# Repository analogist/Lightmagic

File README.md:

# Lightmagic
A safety-isolated dual-channel flexible audio and photodiode trigger for electrophysiological recording time synchronization and verification

## Design
The board has 2 inputs: a mono audio trigger (3.5mm / 1/8" jack, stereo combined) and a photodiode.

The photodiode is generally mounted to a screen or other photo synchronization trigger, and its sensitivity is adjustable with a trim pot. It's powered by a single regulated >5V low voltage source, usually a 9V battery. The audio jack is plugged into an audio synchronization trigger, and looks for any (3Hz highpassed) audio input higher than 0.7V. The audio half is powered by a mini-USB cable which may be hooked up to wall AC at some point, and the entire audio input is optically isolated from the photo trigger half of the board.

The output is an additional 3.5mm (1/8") audio jack with the L channel (tip) carrying the (rectified, amplified, isolated) audio trigger signal and the R channel (ring) carrying the (amplified) photodiode signal. Both channel should swing from 0 (off) - 2V (trigger on) with the standard BOM items.

The design allows for this board to be "trigger glue" between a psychophysical presentation (audio or on-screen stimuli) and electrophysiological recording systems when sub-millisecond synchronization is required, such as for neurostimulation. Note that output voltages are still in the 2V range; this should be further reduced as close as possible to the recording system via passive voltage dividers down to safe voltages and currents (hopefully <50μA for all failure conditions) for in-vivo recordings.

## Files

The source Eagle CAD files are in the `eagle` directory.
The OSH Park-compatible `ger` and `xln` files can be found in the `gerber` directory. Zipping it will allow for manufacture.

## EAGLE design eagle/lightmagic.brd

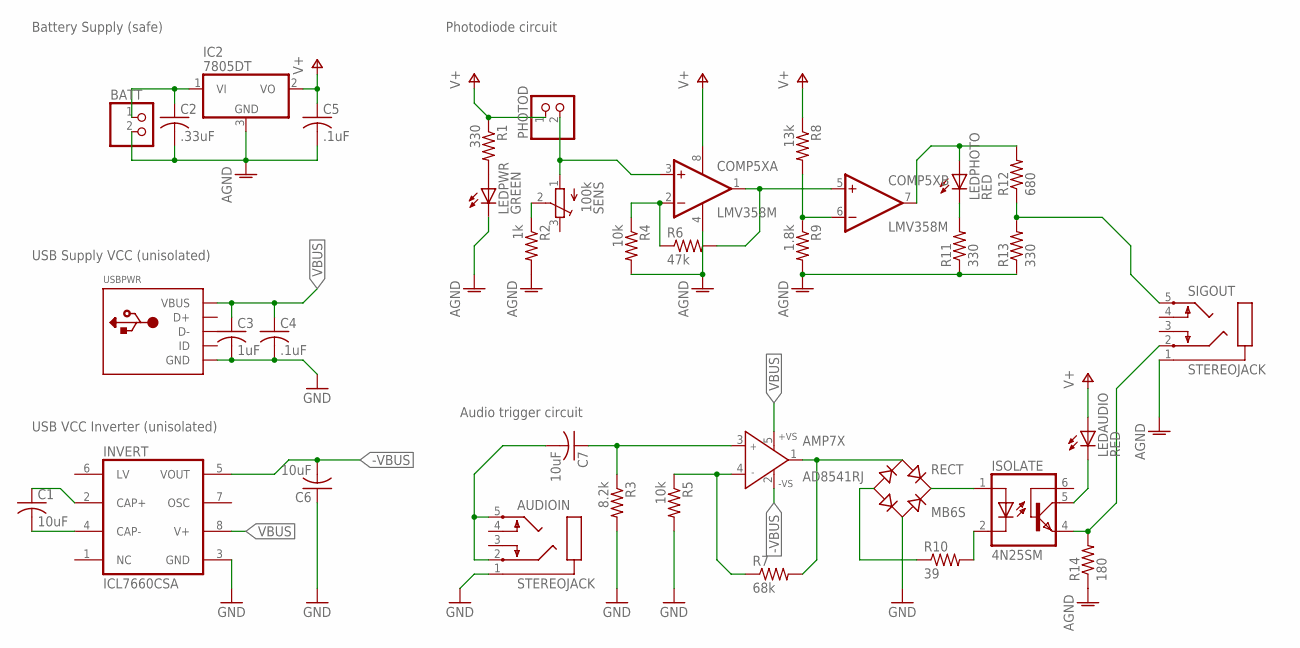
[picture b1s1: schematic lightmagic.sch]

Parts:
AMP7X: AD8541RJ; SOT23-5; MPN AD8541ARTZ-R2
AUDIOIN: STEREOJACK; STX3100; MPN 35RAPC4BHN2
BATT: PINHD-1X2; 1X02; MPN 640456-2
C1, C6, C7: 10uF; C0805; MPN GRT21BR61E106KE13L
C2: .33uF; C0805; MPN MC0805B334K500CT
C3: 1uF; C0805; MPN C0805X104K3RAC3316
C4, C5: .1uF; C0805; MPN 0805YC104KAT2A
COMP5X: LMV358M; SO08; MPN LMV358M
IC2: 7805DT; TO252; MPN MC7805CDTG
INVERT: ICL7660CSA; SO08; MPN LMC7660IM/NOPB
ISOLATE: 4N25SM; DIL6-SMD; MPN 4N25-300E
LEDAUDIO: RED; CHIP-LED0805; MPN QTLP630C7TR
LEDPHOTO: RED; CHIP-LED0805; MPN QTLP630C7TR
LEDPWR: GREEN; CHIP-LED0805; MPN QTLP630C7TR
PHOTOD: PINHD-1X2; 1X02; MPN 640456-2
R1, R11, R13: 330; R0805; MPN ERJ-6ENF3300V
R2: 1k; R0805; MPN ERJ-6ENF12R0V
R3: 8.2k; R0805; MPN MC01W080518K2
R4, R5: 10k; R0805; MPN CRCW080510K0FKTA
R6: 47k; R0805; MPN CRCW080547K0FKEA
R7: 68k; R0805; MPN CRCW080568K0FKEA
R8: 13k; R0805; MPN CRCW080513K0FKEA
R9: 1.8k; R0805; MPN CRCW08051K80FKEA
R10: 39; R0805; MPN ERJ-6GEYJ390V
R12: 680; R0805; MPN ERA-6AEB681V
R14: 180; R0805; MPN CRCW0805180RJNEA
RECT: MB6S; SOIC-4; MPN MB6S
SENS: 100k; TC33X; MPN CRCW0805100KJNEA
SIGOUT: STEREOJACK; STX3100; MPN 35RAPC4BHN2
USBPWR: USBMINIB; USB-MINIB; MPN 1734035-1

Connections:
-VBUS: AMP7X.2 (-VS), C6.2, INVERT.5 (VOUT)
AGND: BATT.2, C2.2, C5.2, COMP5X.4 (V-), IC2.3 (GND), LEDPWR.C, R2.2, R4.2, R9.2, R11.1, R13.1, R14.1, SIGOUT.1
GND: AUDIOIN.1, C3.2, C4.2, C6.1, INVERT.3 (GND), R3.2, R5.2, RECT.~2 (AC2), USBPWR.GND
unnamed: AMP7X.4 (IN-), R5.1, R7.1
unnamed: C1.1, INVERT.2 (CAP+)
unnamed: C1.2, INVERT.4 (CAP-)
unnamed: AUDIOIN.2, AUDIOIN.5, C7.2
unnamed: AMP7X.3 (IN+), C7.1, R3.1
unnamed: AMP7X.1 (OUT), R7.2, RECT.~1 (AC1)
unnamed: ISOLATE.1 (A), RECT.+
unnamed: ISOLATE.2 (C), R10.2
unnamed: R10.1, RECT.-
unnamed: BATT.1, C2.1, IC2.1 (VI)
unnamed: R2.1, SENS.2 (S)
unnamed: LEDPWR.A, R1.2
unnamed: COMP5X.3 (+IN), PHOTOD.2, SENS.1 (A)
unnamed: COMP5X.2 (-IN), R4.1, R6.1
unnamed: COMP5X.1 (OUT), COMP5X.5 (+IN), R6.2
unnamed: COMP5X.6 (-IN), R8.2, R9.1
unnamed: ISOLATE.4 (EMI), R14.2, SIGOUT.2
unnamed: ISOLATE.5 (COL), LEDAUDIO.C
unnamed: LEDPHOTO.C, R11.2
unnamed: R12.1, R13.2, SIGOUT.5
unnamed: COMP5X.7 (OUT), LEDPHOTO.A, R12.2
V+: C5.1, COMP5X.8 (V+), IC2.2 (VO), LEDAUDIO.A, PHOTOD.1, R1.1, R8.1
VBUS: AMP7X.5 (+VS), C3.1, C4.1, INVERT.8 (V+), USBPWR.VBUS

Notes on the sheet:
Battery Supply (safe)
USB VCC Inverter (unisolated)
USB Supply VCC (unisolated)
Photodiode circuit
Audio trigger circuit

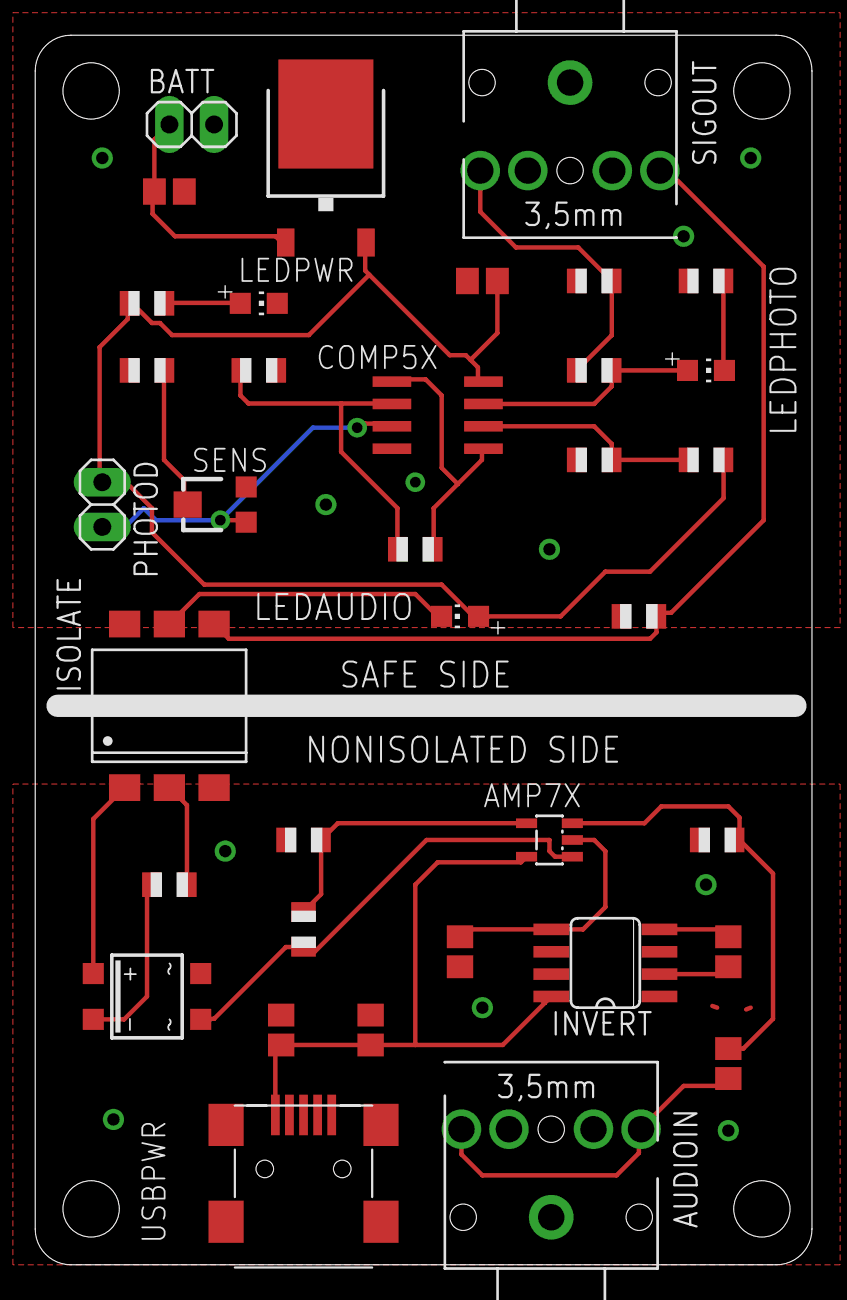
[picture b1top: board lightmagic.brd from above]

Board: 2 copper layers, 44.1 x 69.8 mm, 36 parts (0 on the bottom side), 26 nets.

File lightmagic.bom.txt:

Part     Value      Device          Package      Description                                                                   MF                      MPN                OC_FARNELL OC_NEWARK
AMP7X    AD8541RJ   AD8541RJ        SOT23-5      General-Purpose CMOS Rail-to-Rail Amplifiers                                                          AD8541ARTZ-R2      1464963    28X4209  
AUDIOIN  STEREOJACK STEREOJACK      STX3100      MIC/HEADPHONE JACK                                                            SWITCHCRAFT             35RAPC4BHN2                   96F9607  
BATT                PINHD-1X2       1X02         PIN HEADER                                                                    TYCO ELECTRONICS        640456-2                      90F4250  
C1       10uF       C-USC0805       C0805        CAPACITOR, American symbol                                                                            GRT21BR61E106KE13L            01AC8983 
C2       .33uF      C-USC0805       C0805        CAPACITOR, American symbol                                                                            MC0805B334K500CT              06X6218  
C3       1uF        C-USC0805       C0805        CAPACITOR, American symbol                                                                            C0805X104K3RAC3316            01AC1593 
C4       .1uF       C-USC0805       C0805        CAPACITOR, American symbol                                                                            0805YC104KAT2A                05AC9650 
C5       .1uF       C-USC0805       C0805        CAPACITOR, American symbol                                                                            0805YC104KAT2A                05AC9650 
C6       10uF       C-USC0805       C0805        CAPACITOR, American symbol                                                                            GRT21BR61E106KE13L            01AC8983 
C7       10uF       C-USC0805       C0805        CAPACITOR, American symbol                                                                            GRT21BR61E106KE13L            01AC8983 
COMP5X   LMV358M    LMV358M         SO08         Dual General Purpose, Low Voltage, Rail-to-Rail Output Operational Amplifiers                         LMV358M                       97K3153  
IC2      7805DT     7805DT          TO252        Positive VOLTAGE REGULATOR                                                    ON SEMICONDUCTOR        MC7805CDTG                    71J5739  
INVERT   ICL7660CSA ICL7660CSA      SO08         VOLTAGE CONVERTER                                                             NATIONAL SEMICONDUCTOR  LMC7660IM/NOPB     9724710    41K2738  
ISOLATE  4N25SM     4N25SM          DIL6-SMD     General Purpose 6-Pin Phototransistor Optocouplers                                                    4N25-300E          1021152    13M5766  
LEDAUDIO RED        LEDCHIP-LED0805 CHIP-LED0805 LED                                                                                                   QTLP630C7TR                   01AC7976 
LEDPHOTO RED        LEDCHIP-LED0805 CHIP-LED0805 LED                                                                                                   QTLP630C7TR                   01AC7976 
LEDPWR   GREEN      LEDCHIP-LED0805 CHIP-LED0805 LED                                                                                                   QTLP630C7TR                   01AC7976 
PHOTOD              PINHD-1X2       1X02         PIN HEADER                                                                    TYCO ELECTRONICS        640456-2                      90F4250  
R1       330        R-US_R0805      R0805        RESISTOR, American symbol                                                                             ERJ-6ENF3300V                 90W3413  
R2       1k         R-US_R0805      R0805        RESISTOR, American symbol                                                                             ERJ-6ENF12R0V                 64R5373  
R3       8.2k       R-US_R0805      R0805        RESISTOR, American symbol                                                     Multicomp Passives      MC01W080518K2                 58K4911  
R4       10k        R-US_R0805      R0805        RESISTOR, American symbol                                                     VISHAY/DALE             CRCW080510K0FKTA              05F1511  
R5       10k        R-US_R0805      R0805        RESISTOR, American symbol                                                     VISHAY/DALE             CRCW080510K0FKTA              05F1511  
R6       47k        R-US_R0805      R0805        RESISTOR, American symbol                                                     VISHAY/DALE             CRCW080547K0FKEA              42K4553  
R7       68k        R-US_R0805      R0805        RESISTOR, American symbol                                                     VISHAY/DALE             CRCW080568K0FKEA              53K0428  
R8       13k        R-US_R0805      R0805        RESISTOR, American symbol                                                     VISHAY/DALE             CRCW080513K0FKEA              42K4278  
R9       1.8k       R-US_R0805      R0805        RESISTOR, American symbol                                                     VISHAY/DALE             CRCW08051K80FKEA              42K4228  
R10      39         R-US_R0805      R0805        RESISTOR, American symbol                                                                             ERJ-6GEYJ390V                 53W4957  
R11      330        R-US_R0805      R0805        RESISTOR, American symbol                                                                             ERJ-6ENF3300V                 90W3413  
R12      680        R-US_R0805      R0805        RESISTOR, American symbol                                                                             ERA-6AEB681V                  08N2184  
R13      330        R-US_R0805      R0805        RESISTOR, American symbol                                                                             ERJ-6ENF3300V                 90W3413  
R14      180        R-US_R0805      R0805        RESISTOR, American symbol                                                     VISHAY/DALE             CRCW0805180RJNEA              01H7775  
RECT     MB6S       MB6S            SOIC-4       Bridge Rectifier                                                              FAIRCHILD SEMICONDUCTOR MB6S                          58K1814  
SENS     100k       TRIMPOTTC33X    TC33X        SMT trimmer potentiometer part number TC33X                                                           CRCW0805100KJNEA              04M8142  
SIGOUT   STEREOJACK STEREOJACK      STX3100      MIC/HEADPHONE JACK                                                            SWITCHCRAFT             35RAPC4BHN2                   96F9607  
USBPWR              USBMINIB        USB-MINIB    USB Connectors                                                                                        1734035-1                     16M2760

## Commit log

2017-05-15 Lightmagic v0.1, first prototype
2017-05-15 v0.1.1, fixed some paths and positions
2017-05-15 update parts list, miter corners
2017-05-15 add BOM, order, images
2017-05-15 Update README.md with design
2017-05-15 Update README.md with image layout
2017-05-15 Correct L/R output and add file explanations
2017-05-15 add ltspice files
2017-05-16 reroute audio side
2017-07-02 create images dir
2017-07-02 update image location
